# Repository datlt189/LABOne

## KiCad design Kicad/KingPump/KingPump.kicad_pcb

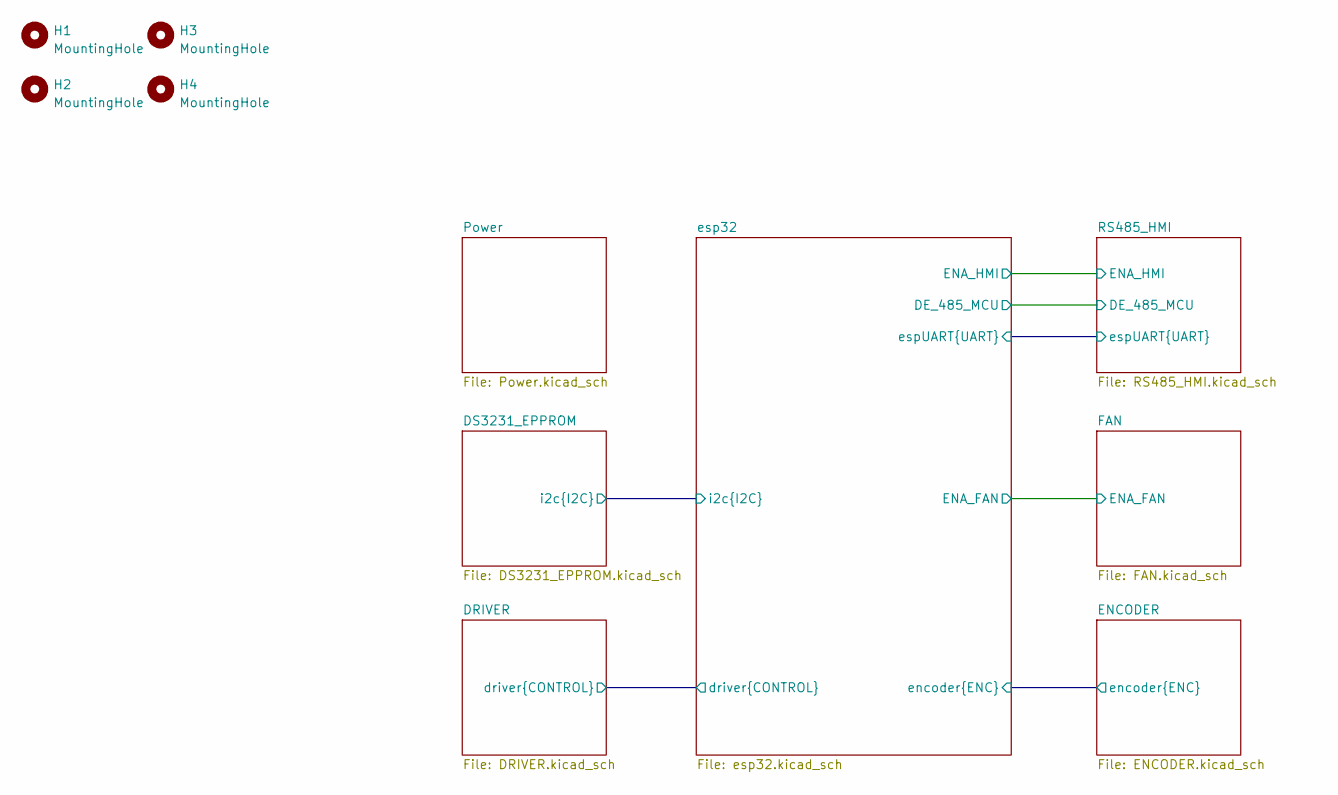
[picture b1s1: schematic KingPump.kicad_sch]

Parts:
H1, H2, H3, H4: MountingHole; MountingHole_3.2mm_M3_Pad_Via

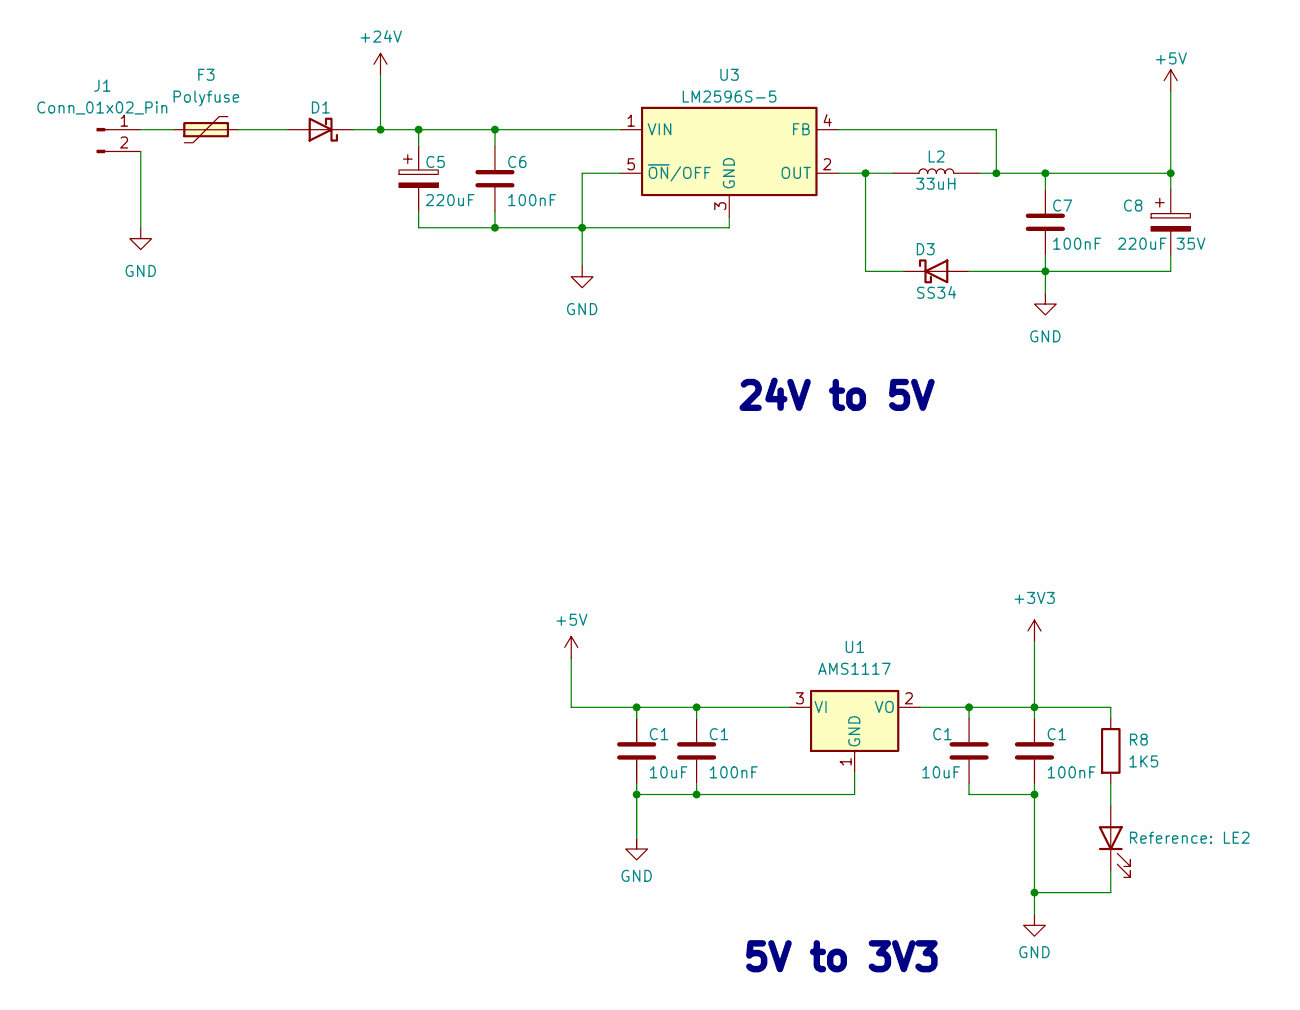
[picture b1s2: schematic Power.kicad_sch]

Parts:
C1: 10uF; C_0603
C5: 220uF; CP_Alu_SMD_8x10.5mm
C6, C7: 100nF; C_1206
C8: 220uF 35V; CP_Alu_SMD_8x10.5mm
D1: SS56; D_SMA
D3: SS34; D_SMA
F3: Polyfuse; Fuse_1812_4532Metric
J1: Conn_01x02_Pin; TerminalBlock_Phoenix_MKDS-1,5-2-5.08_1x02_P5.08mm_Horizont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
L2: 33uH; L_Bourns_SRR1260
LE2: Led; LED_0603
R8: 1K5; R_0603
U1: AMS1117; SOT233
U3: LM2596S-5; TO-263-5_TabPin3

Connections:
+24V: C5.1, C6.1, D1.1 (K), U3.1 (VIN); also elsewhere on the board
GND: C1.2, C5.2, C6.2, C7.2, C8.2, D3.2 (A), J1.2, LE2.1 (K), U1.1 (GND), U3.3 (GND), U3.5 (~ON/OFF); also elsewhere on the board
unnamed: D1.2 (A), F3.2
unnamed: D3.1 (K), L2.1, U3.2 (OUT)
unnamed: F3.1, J1.1
unnamed: LE2.2 (A), R8.2

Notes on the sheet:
5V to 3V3
24V to 5V

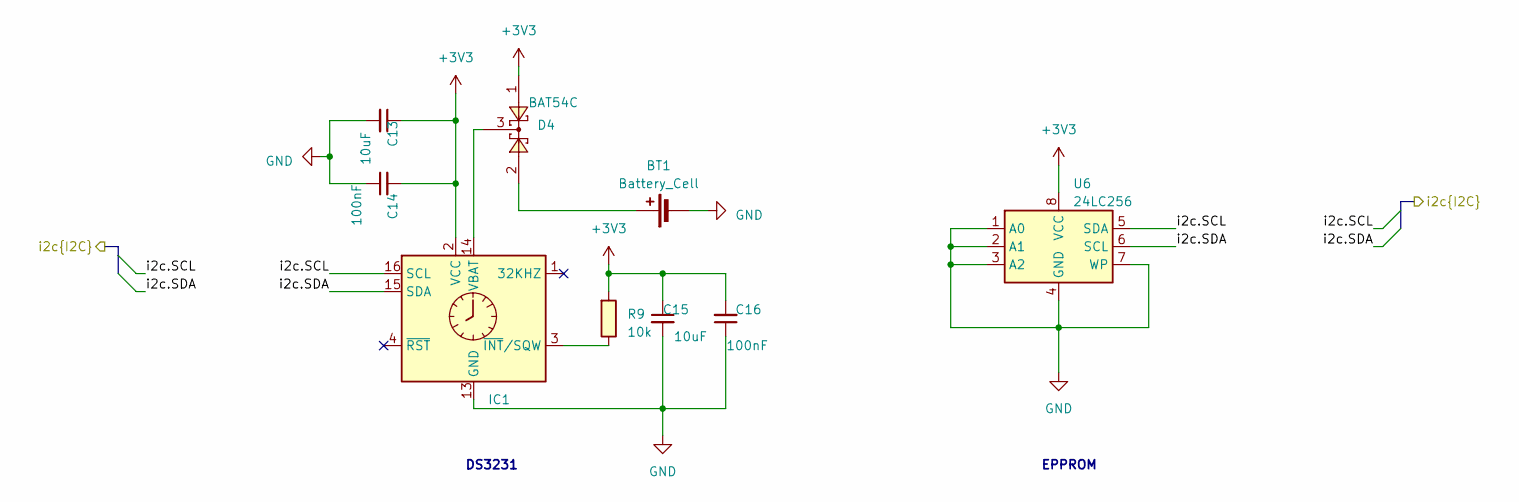
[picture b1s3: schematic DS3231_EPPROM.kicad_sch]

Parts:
BT1: Battery_Cell; BatteryHolder_CR1220
C13, C15: 10uF; C_0603
C14, C16: 100nF; C_0603
D4: BAT54C; SOT23-3
IC1: RTC_DS3231M; SOIC-16W_7.5x10.3mm_P1.27mm
R9: 10k; R_0603
U6: 24LC256; SOIC-8_3.9x4.9mm_P1.27mm

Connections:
/DS3231_EPPROM/i2c.SCL: IC1.16 (SCL), U6.5 (SDA); also elsewhere on the board
/DS3231_EPPROM/i2c.SDA: IC1.15 (SDA), U6.6 (SCL); also elsewhere on the board
GND: BT1.2 (-), C13.2, C14.1, C15.2, C16.1, IC1.5 (GND), IC1.6 (GND), IC1.7 (GND), IC1.8 (GND), IC1.9 (GND), IC1.10 (GND), IC1.11 (GND), IC1.12 (GND), IC1.13 (GND), U6.1 (A0), U6.2 (A1), U6.3 (A2), U6.4 (GND), U6.7 (WP); also elsewhere on the board
unnamed: BT1.1 (+), D4.2
unnamed: D4.3, IC1.14 (VBAT)
unnamed: IC1.3 (~INT/SQW), R9.2

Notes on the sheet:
EPPROM
DS3231

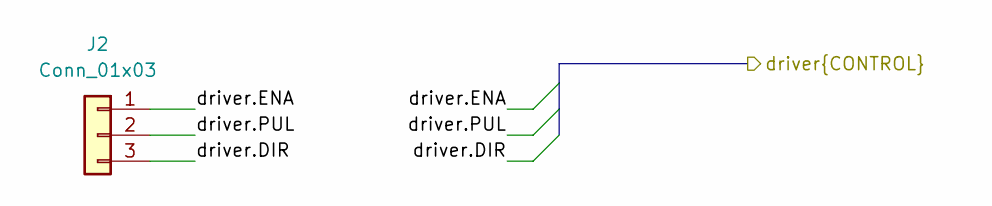
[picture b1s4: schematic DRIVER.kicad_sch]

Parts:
J2: Conn_01x03; Conn_XH-P2.54mm-3P

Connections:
/DRIVER/driver.DIR: J2.3; also elsewhere on the board
/DRIVER/driver.ENA: J2.1; also elsewhere on the board
/DRIVER/driver.PUL: J2.2; also elsewhere on the board

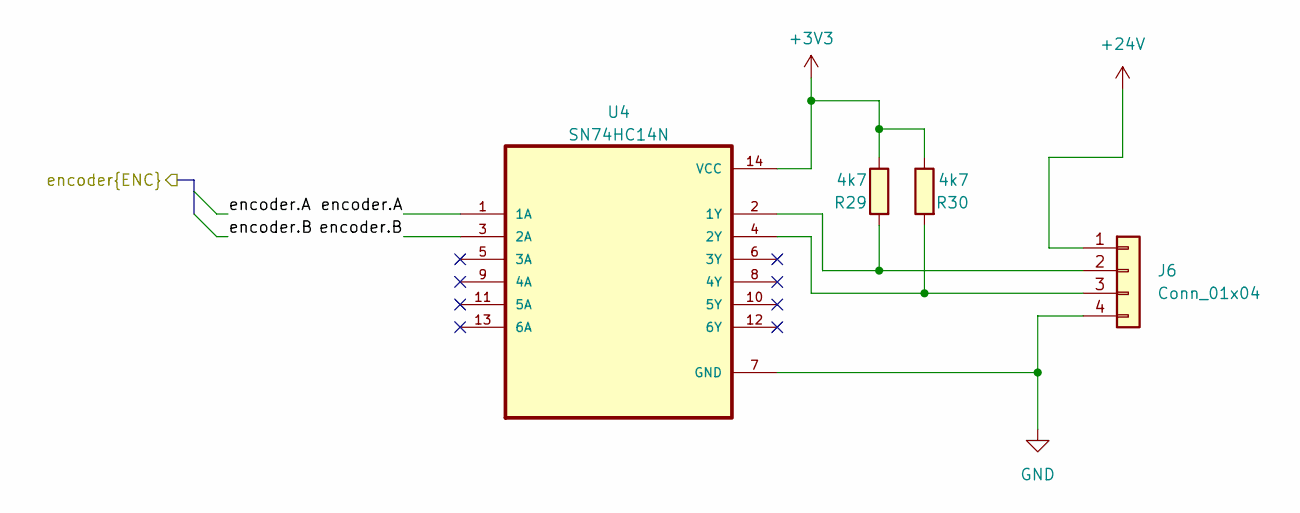
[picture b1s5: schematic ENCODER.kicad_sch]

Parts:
J6: Conn_01x04; Conn_XH-P2.54mm-4P
R29, R30: 4k7; R_0603
U4: SN74HC14N; DIP794W45P254L1930H508Q14

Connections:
+24V: J6.1; also elsewhere on the board
/ENCODER/encoder.A: U4.1 (1A); also elsewhere on the board
/ENCODER/encoder.B: U4.3 (2A); also elsewhere on the board
GND: J6.4, U4.7 (GND); also elsewhere on the board
unnamed: J6.2, R29.1, U4.2 (1Y)
unnamed: J6.3, R30.1, U4.4 (2Y)

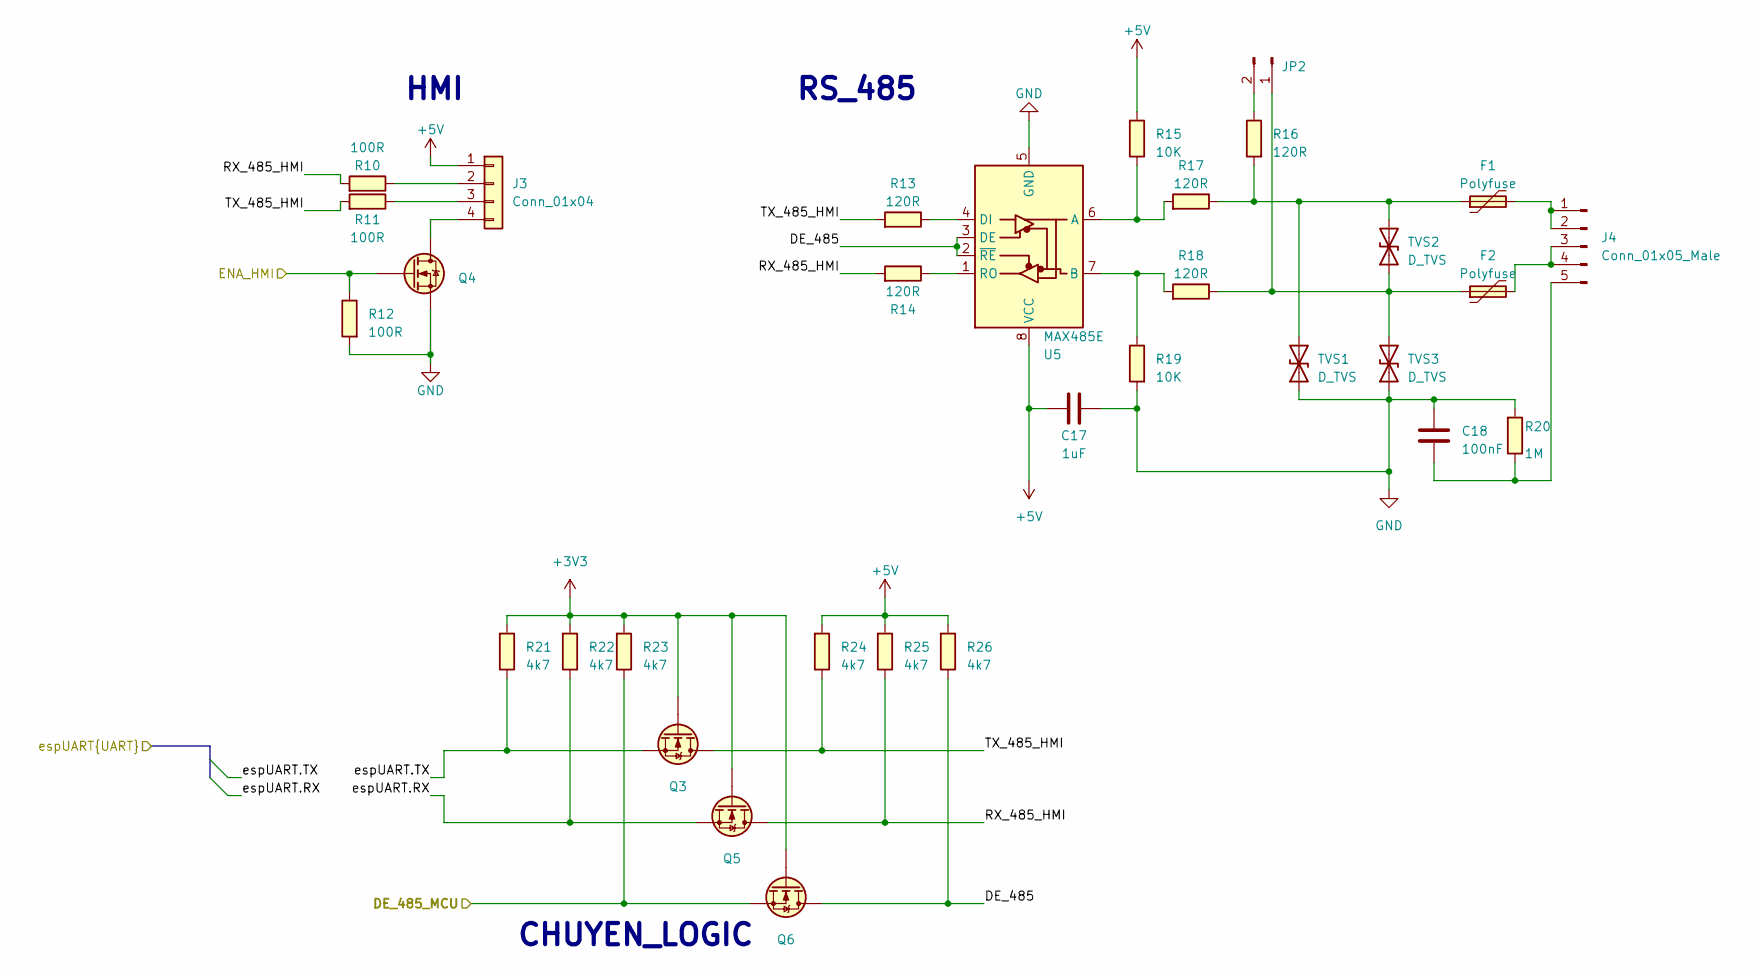
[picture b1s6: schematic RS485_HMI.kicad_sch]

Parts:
C17: 1uF; C_0603
C18: 100nF; C_0603
F1, F2: Polyfuse; Fuse_1812_4532Metric
J3: Conn_01x04; Conn_XH-P2.54mm-4P
J4: Conn_01x05_Male; Conn_XH-P2.54mm-5P
JP2: Conn_01x02_Male; SolderJumper-2_P1.3mm_Open_RoundedPad1.0x1.5mm
Q3, Q4, Q5, Q6: N_Mosfet; SOT23-3
R10, R11, R12: 100R; R_0603
R13, R14, R16, R17, R18: 120R; R_0603
R15, R19: 10K; R_0603
R20: 1M; R_0603
R21, R22, R23, R24, R25, R26: 4k7; R_0603
TVS1, TVS2, TVS3: D_TVS; D_SMA
U5: MAX485E; SOIC-8_3.9x4.9mm_P1.27mm

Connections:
/RS485_HMI/DE_485: Q6.3 (D), R26.2, U5.2 (~RE), U5.3 (DE)
/RS485_HMI/DE_485_MCU: Q6.2 (S), R23.2; also elsewhere on the board
/RS485_HMI/ENA_HMI: Q4.1 (G), R12.2; also elsewhere on the board
/RS485_HMI/RX_485_HMI: Q5.3 (D), R10.1, R14.1, R25.2
/RS485_HMI/TX_485_HMI: Q3.3 (D), R11.1, R13.1, R24.2
/RS485_HMI/espUART.RX: Q5.2 (S), R22.2; also elsewhere on the board
/RS485_HMI/espUART.TX: Q3.2 (S), R21.2; also elsewhere on the board
GND: C17.2, C18.1, Q4.2 (S), R12.1, R19.1, R20.1, TVS1.1 (A1), TVS3.1 (A1), U5.5 (GND); also elsewhere on the board
unnamed: J3.2, R10.2
unnamed: J3.3, R11.2
unnamed: J3.4, Q4.3 (D)
unnamed: F1.2, J4.1, J4.2
unnamed: F2.2, J4.3, J4.4
unnamed: C18.2, J4.5, R20.2
unnamed: F2.1, JP2.1, R18.2, TVS2.1 (A1), TVS3.2 (A2)
unnamed: JP2.2, R16.2
unnamed: F1.1, R16.1, R17.2, TVS1.2 (A2), TVS2.2 (A2)
unnamed: R15.2, R17.1, U5.6 (A)
unnamed: R18.1, R19.2, U5.7 (B)
unnamed: R13.2, U5.4 (DI)
unnamed: R14.2, U5.1 (RO)

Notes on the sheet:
CHUYEN_LOGIC
HMI
RS_485

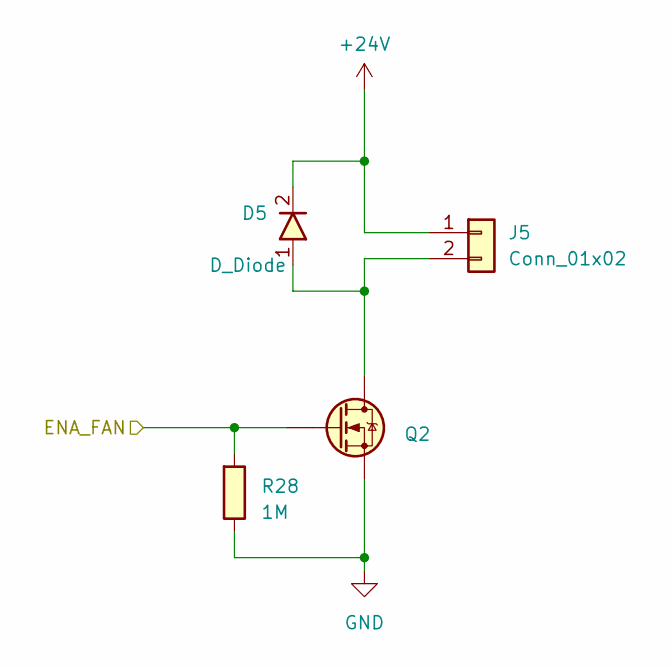
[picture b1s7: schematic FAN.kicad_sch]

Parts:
D5: D_Diode; SOD-123F
J5: Conn_01x02; Conn_XH-P2.54mm-2P
Q2: N_Mosfet; SOT23-3
R28: 1M; R_0603

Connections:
+24V: D5.2, J5.1; also elsewhere on the board
/FAN/ENA_FAN: Q2.1 (G), R28.1; also elsewhere on the board
GND: Q2.2 (S), R28.2; also elsewhere on the board
unnamed: D5.1, J5.2, Q2.3 (D)

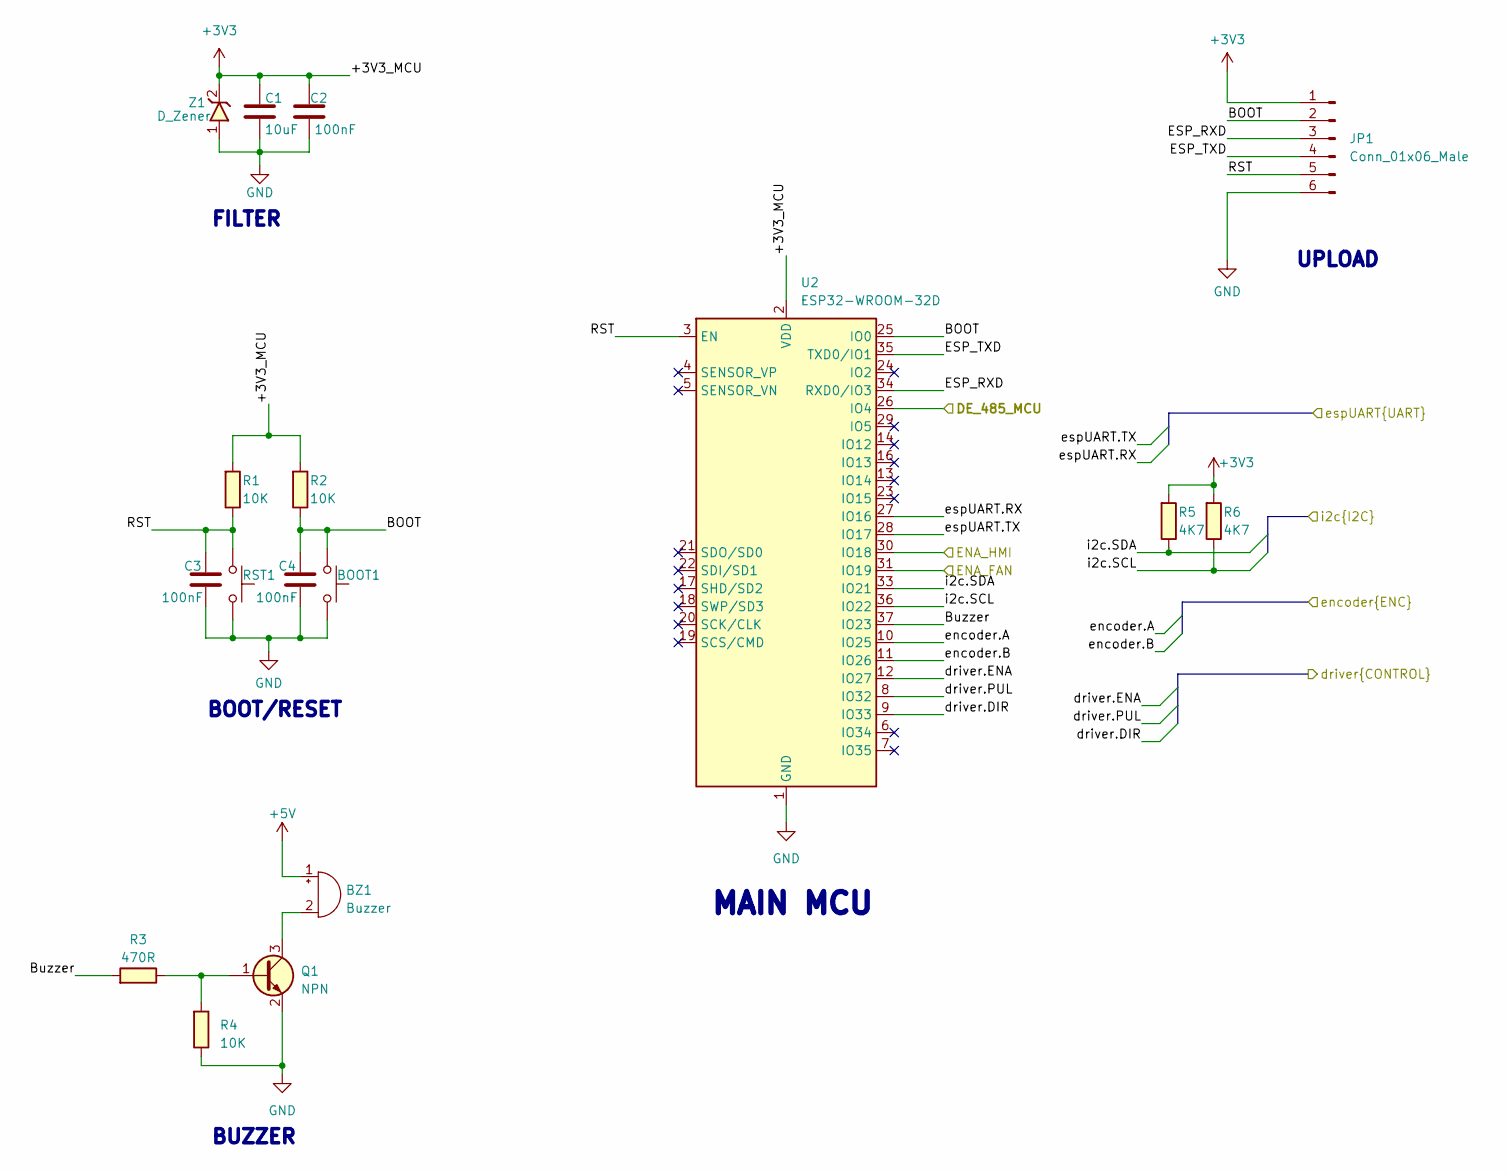
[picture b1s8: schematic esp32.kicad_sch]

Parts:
BOOT1: SW_Push; SW_SPST_PTS810
BZ1: Buzzer; Buzzer_12x9.5RM7.6
C1: 10uF; C_0603
C2, C3, C4: 100nF; C_0603
JP1: Conn_01x06_Male; XH_6P_2.54mm_Vertical
Q1: NPN; SOT23-3
R1, R2, R4: 10K; R_0603
R3: 470R; R_0603
R5, R6: 4K7; R_0603
RST1: SW_Push; SW_SPST_PTS810
U2: ESP32-WROOM-32D; ESP32-WROOM-32
Z1: D_Zener; D_SOD-123F

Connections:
/DRIVER/driver.DIR: U2.9 (IO33); also elsewhere on the board
/DRIVER/driver.ENA: U2.12 (IO27); also elsewhere on the board
/DRIVER/driver.PUL: U2.8 (IO32); also elsewhere on the board
/DS3231_EPPROM/i2c.SCL: R6.2, U2.36 (IO22); also elsewhere on the board
/DS3231_EPPROM/i2c.SDA: R5.2, U2.33 (IO21); also elsewhere on the board
/ENCODER/encoder.A: U2.10 (IO25); also elsewhere on the board
/ENCODER/encoder.B: U2.11 (IO26); also elsewhere on the board
/FAN/ENA_FAN: U2.31 (IO19); also elsewhere on the board
/RS485_HMI/DE_485_MCU: U2.26 (IO4); also elsewhere on the board
/RS485_HMI/ENA_HMI: U2.30 (IO18); also elsewhere on the board
/RS485_HMI/espUART.RX: U2.27 (IO16); also elsewhere on the board
/RS485_HMI/espUART.TX: U2.28 (IO17); also elsewhere on the board
/esp32/BOOT: BOOT1.1, C4.1, JP1.2, R2.2, U2.25 (IO0)
/esp32/Buzzer: R3.1, U2.37 (IO23)
/esp32/ESP_RXD: JP1.3, U2.34 (RXD0/IO3)
/esp32/ESP_TXD: JP1.4, U2.35 (TXD0/IO1)
/esp32/RST: C3.1, JP1.5, R1.2, RST1.1, U2.3 (EN)
GND: BOOT1.2, C1.2, C2.2, C3.2, C4.2, JP1.6, Q1.2 (E), R4.2, RST1.2, U2.1 (GND), U2.15 (GND), U2.38 (GND), U2.39 (GND), Z1.1; also elsewhere on the board
unnamed: BZ1.2 (+), Q1.3 (C)
unnamed: Q1.1 (B), R3.2, R4.1

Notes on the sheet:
BOOT/RESET
UPLOAD
BUZZER
MAIN MCU
FILTER

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
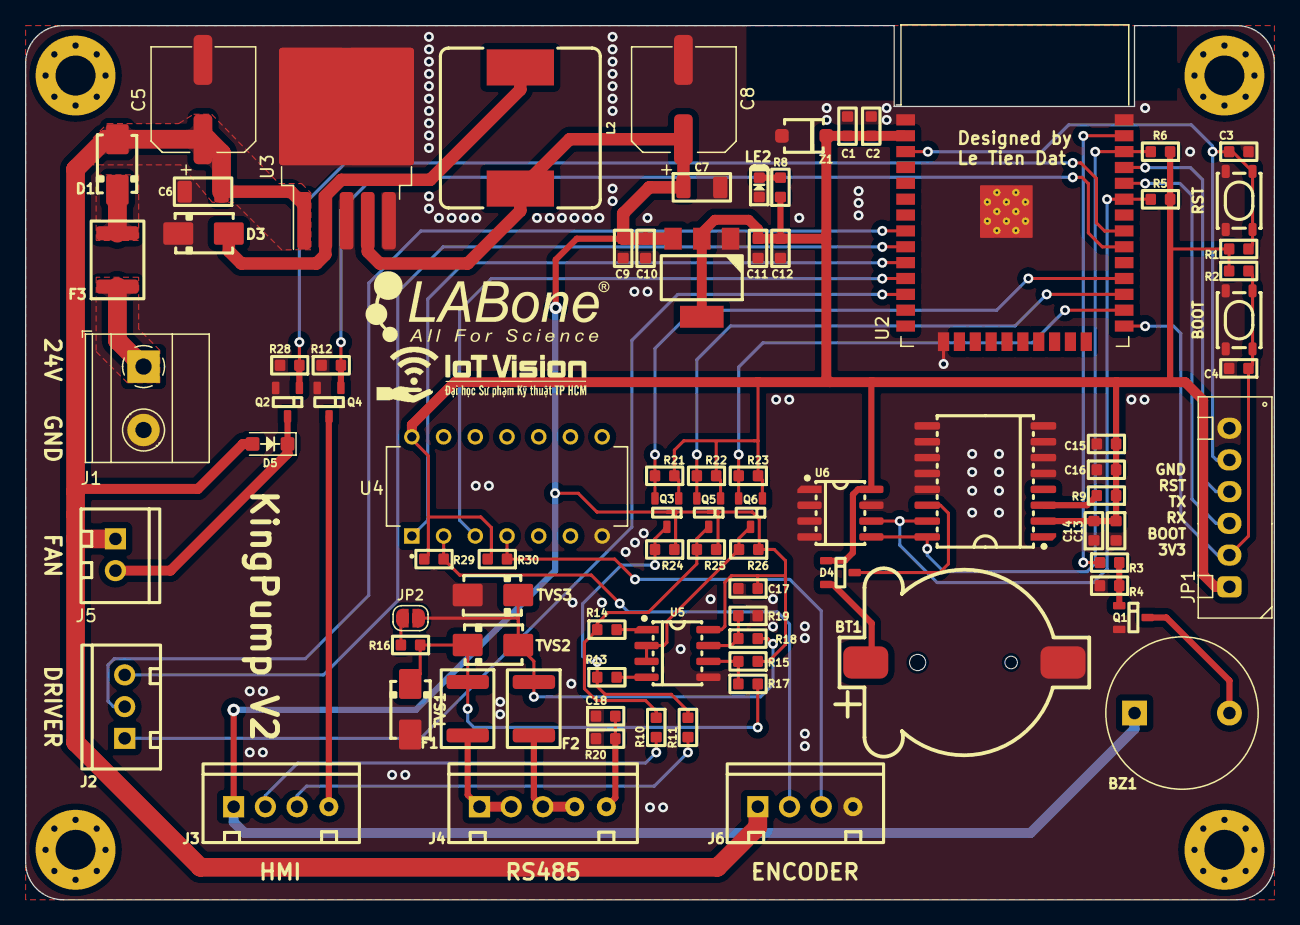
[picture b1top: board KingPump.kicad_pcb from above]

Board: 2 copper layers, 100.0 x 70.0 mm, 88 parts (0 on the bottom side), 49 nets.

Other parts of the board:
C9, C11: 10uF; C_0603
C10, C12: 100nF; C_0603

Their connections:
GND: C9.2, C10.2, C11.2, C12.2; also elsewhere on the board

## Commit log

2023-09-28 upload LABOne

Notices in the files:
parts and their libraries:
Copyright 2021 Accelerated Designs. All rights reserved.
